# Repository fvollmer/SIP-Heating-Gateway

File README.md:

SIP Heating Gateway
====================

This device allows you to control the heating (or any other device) by calling in and using an interactive voice menu. In case of a power loss the last state will be restored as soon as the power is back. The software is build to survive unexpected power losses.

The heart of the system is a Raspberry pi with a custom hat to provide 12V to an external relay. On this Raspberry pi a custom embedded linux is used to to control the 12V via a small shell script. It connects via ethernet to the a SIP server (e.g. a fritzbox router or your isp). The heavy lifting for the SIP connection and the voice menu is done by asterisk, which uses the already mentioned shell script to switch a gpio pin. The linux system is build with buildroot and the hole image image is less than 200MB and boots in a few seconds.

The linux system on the raspberry pi is configured to use the micro sd card as read only storage. This should prevent damage on power failure. The only exception is a persitent partition, which is used to save the current state. This state will be restored in case of a power failure. The partition should also be safe from corruption due to the mount parameters and the infrequent writes.

## Usage

Connect Power (5V via micro-USB and 12V), ethernet and the output to the relay. After bootup the device accepts incoming calls.

Call the device,  wait until pickup and follow the voice instructions:
1. Enter the PIN and press `#`
2. Press `1` to turn the heating on, `2` to turn the heating off, `3` to get the status of the heating
3. Repeat step 2, or hang up

After a timeout the caller will be disconnected automatically.

```
                                               5V (micro USB)
                                                |
                                                v
+-----------------+                      +----------------+              +----------+
| router / switch | SIP (over ethernet)  | Raspberry Pi   | 12V Switched | Relay of |
| e.g. fritzbox   |<-------------------->| (with 12V hat) |------------->| heating  |
+-----------------+                      +----------------+              +----------+
                                                ^
                                                |
                                              12 V
```

## Configuration
The custom embedded system is based on buildroot. The behaviour at a call is controlled by [Asterisk](https://www.asterisk.org/). There are two main configuration files:
 * `/etc/asterisk/sip.conf`
   SIP server configuration
 * `/etc/asterisk/extensions.conf`
   Dialplan (phone menu, pin)

The configuration files can be adjusted by changing the files of the overlay (`br-external/board/raspberrypi-heating-control/rootfs-overlay`). Asterisk is configured to only use a minimal amount of modules. Modify `/etc/asterisk/modules.conf` if necessary.

There is a watchdog script (`/opt/heatingControl/asterisk_wdog`) that monitors the peers and registry and will restart asterisk in case of failures. It is automatically started at boot via `/etc/init.d/S55asterisk_wdog`. You probably want to stop it to configure asterisk and start it after the finished configuration.

For maintenace and debugging it is possible to connect to the device via a serial connection (115200 8N1) or HDMI. The system is by default read-only. To modify the file system it has to be remounted (`mount -o remount,rw /`). The login data is:

 * username: "root"
 * password: "" (There is no root password. This is no problem, because there is no way to login remotely)

## How to build the sd card image
You can build the sd card image yourself by cross compiling it on your pc. Depending on your hardware configuration this may take a while. Simply follow these steps:
1. Clone repository (use `--recursive` to get buildroot submodule)
2. Change into software folder (`cd software`)
3. `make BR2_EXTERNAL=$PWD/br-external -C buildroot raspberrypi23-heating-control_defconfig`
4. `make -C buildroot`
5. write `buildroot/output/images/sdcard.img` to sd card (e.g. `dd if=buildroot/output/images/sdcard.img of=/dev/mmcblk0 bs=1M && sync`)

## Hardware
You don't need any special hardware for this. The raspberry pi will just toggle one of the GPIO PINs (see `/opt/heatingControl/controlheating` for details).

The author of this project wants to switch a 12V relay and has designed a hat for this task. This hat is designed to take quite a bit of abuse like e.g. short circuit, reverse power, ESD etc. and can supply 5-24V with up to 1.5A from an external power supply. In practice it should also tolerate higher voltages and currents, but you probably want to check the schematic and datasheets to push the limits. Further it has a manual override switch in case of software issues or a failure of the raspberry pi. Simplified schematic:

Full schematic:

The hardware is designed to fit nicely into a HighPi Case, which has all necessary cutouts and can be mounted on a wall.

## Good to know
 * This system uses [Buildroot](https://buildroot.org/) to create a custom embedded system. This provides more flexibility and allows more customization than a stripped down raspbian. The complete image is just a little bigger than 100MB.
 * Connect via 3.3V serial (115200 8N1) or connect an external monitor via HDMI and use a usb keyboard
 * The heating control script is `/opt/heatingControl/controlheating`
 * The root system is read only. It can be mounted as rw (`mount / -o remount,rw`), but this is mainly recommanded for testing and maybe the initial configuration. Every change can be integrated into `br-external`. This way the image can be build in a repeatable way.
 * There is a small persistent storage partition at the sd card. It is mounted at boot via fstab at `/media/persistent/`. The mount options `rw,sync,data=journal,barrier=1,noatime,commit=1` were choosen to avoid data corruption and wear of the sd card. It is only used to store store the current state at `/media/persistent/last_state` and to restore it after a power loss. On every boot `/etc/init.d/S10restorestate` tries to restore the last state. 
 * To debug problems with asterisk it might be useful to connect to a running asterisk in verbose mode: `asterisk -rvvvv`. You can enable SIP debug mode with `sip set debug on`.
 * Any file can be added/overwritten by adding it ot the rootfs overlay at `br-external/board/raspberrypi2-heating-control/rootfs-overlay/`. 
 * The asterisk configuration files can be found at `/etc/asterisk`. The build process automatically deploys the default configuration files. The overlay is used to overwrite them.
    - SIP configuration file: `/etc/asterisk/sip.conf`
    - Dialplan (phone menu, pin): `/etc/asterisk/extensions.conf`
 * The buildroot configuration is based on the raspberry pi 2 configuration with additions to make it compatible with the raspberry pi 3. Other version can easily be added.
 * eth0 is managed by ifplugd (provided by busybox), which will automatically ifup/ifdown the interface if a network cable is connected/disconnected
 * The dhcp client was configured to run in the background. This is useful if the network link isn't ready when we try to get an ip address. This archived with a custom busybox configuration with the option `CONFIG_IFUPDOWN_UDHCPC_CMD_OPTIONS=-R -b -O search"`. The option `-b` sets udhcpc to run in the background. (`-R` is release on exit, `-O search` enables domain search option RFC 3397)
 * Busybox is configured to ship non default packages:
   - `rx` (in case we want to transfer a file via serial) 
   - `ifplugd` (see above)
 * Aterisk logs to syslog, this avoids filling up our tmpfs. Further cdr (call detail record) is disabled (`/etc/asterisk/cdr.conf`). Busybox rotates syslog for us (CONFIG_FEATURE_ROTATE_LOGFILE)
 * The hardware watchdog of the raspberry pi (bcm2835_wdt) is used to restart the system in case the system locks up. `/etc/init.d/S15watchdog` starts the watchdog at boot and periodically writes to `/dev/watchdog`.

## Overview of files
```
├──.github/workflows
├──audio-gen
├──hardware
└──software
   ├──buildroot
   └──br-external
      ├── board
      │   └── raspberrypi2-heating-control
      │       ├── genimage-raspberrypi2-heating-control.cfg
      │       ├── post-build.sh
      │       ├── post-image.sh
      │       └── rootfs-overlay
      │           └── <config files and scripts>
      ├── Config.in
      ├── configs
      │   └── raspberrypi2-heating-control_defconfig
      ├── external.desc
      └── external.mk
```

 * `.github/workflows` automatic build files
 * `audio-gen` infos about the audio file generation for the interactive voice menu
 * `hardware` pcb files for the 12V hat
 * `buildroot` git submodule of [buildroot](https://buildroot.org/)
 * `br-external` external overlay module for buildroot with all configuration and software files to build our custom linux

## Test cases

After making changes to the image, I like to test and verify that nothing broke by accident. The following test cases prooved to be useful. For now testing is done manually, but it would be an interesting idea to automate them.

 * Check basic functionality
   1. Start Rasbperry Pi with everything connected (including network)
   2. Call and interact with the voice menu
   3. Check authentication, automatic timeout, turn heating on/off, check status of heating
 * Check if state is restored on power loss
   1. Start Rasbperry Pi with everything connected (including network)
   2. Turn heating on
   3. Disconnect power, reconnect power
   4. Check if heating is automatically turned on while booting
   5. Repeat for heating off
 * Simulate power outage
   1. Disconnect Raspberry Pi AND the network infrastructure power
   2. Reconnect everything to power
   3. Check if Raspberry Pi can be called
 * Start Raspberry Pi without network and connect it later
   1. Start Raspberry Pi without network connection
   2. Wait 5 minutes
   3. Connect network connection
   4. Wait 5 minutes (asterisk watch dog will restart asterisk after like 4 minutes)
   5. Check if Raspberry Pi can be called

The previous checks are usually enough, but here are some more:

 * Check ifplugd
   1. Disconnect ethernet cable from running Pi
   2. Check if `ifconfig` if ip address is gone (takes a few seconds)
   3. Reconnect ethernet cable
   4. Check with `ifconfig` if we get a dhcp lease
 * Check asterisk watchdog
   1. Note current PID of asterisk: `pgrep -x asterisk`
   2. Disconnect ethernet cable from running Pi
   3. Check if watchdog complains at syslog (`/var/log/messages`), watchdog only checks asterisk once every 60 seconds
   4. Check if watchdog restarts asterisk after about 4 minutes by comparing the PID
 * Check if syslog is rotated
   1. run `while true; do logger hello; done` for some moments
   2. check if `/var/log/messages` is rotated to `/var/log/messages.0` and if file size is small (like 200kB)

## Enhancement Ideas
 * Add an ssh server to make maintenance easier (at the moment you have to connect via serial or connect your Keyboard and display directly). This ssh server could be enabled by a jumper to enable a maintenance mode.
 * Don't run asterisk as root. This sounds simple in theory, but the user needs permissions to write to /sys/class/gpio. The best way to archive this is probably to use `mdev` together with the `devtmpfs`. On the other hand it won't enhance the security a lot, since asterisk is the only service on this device.

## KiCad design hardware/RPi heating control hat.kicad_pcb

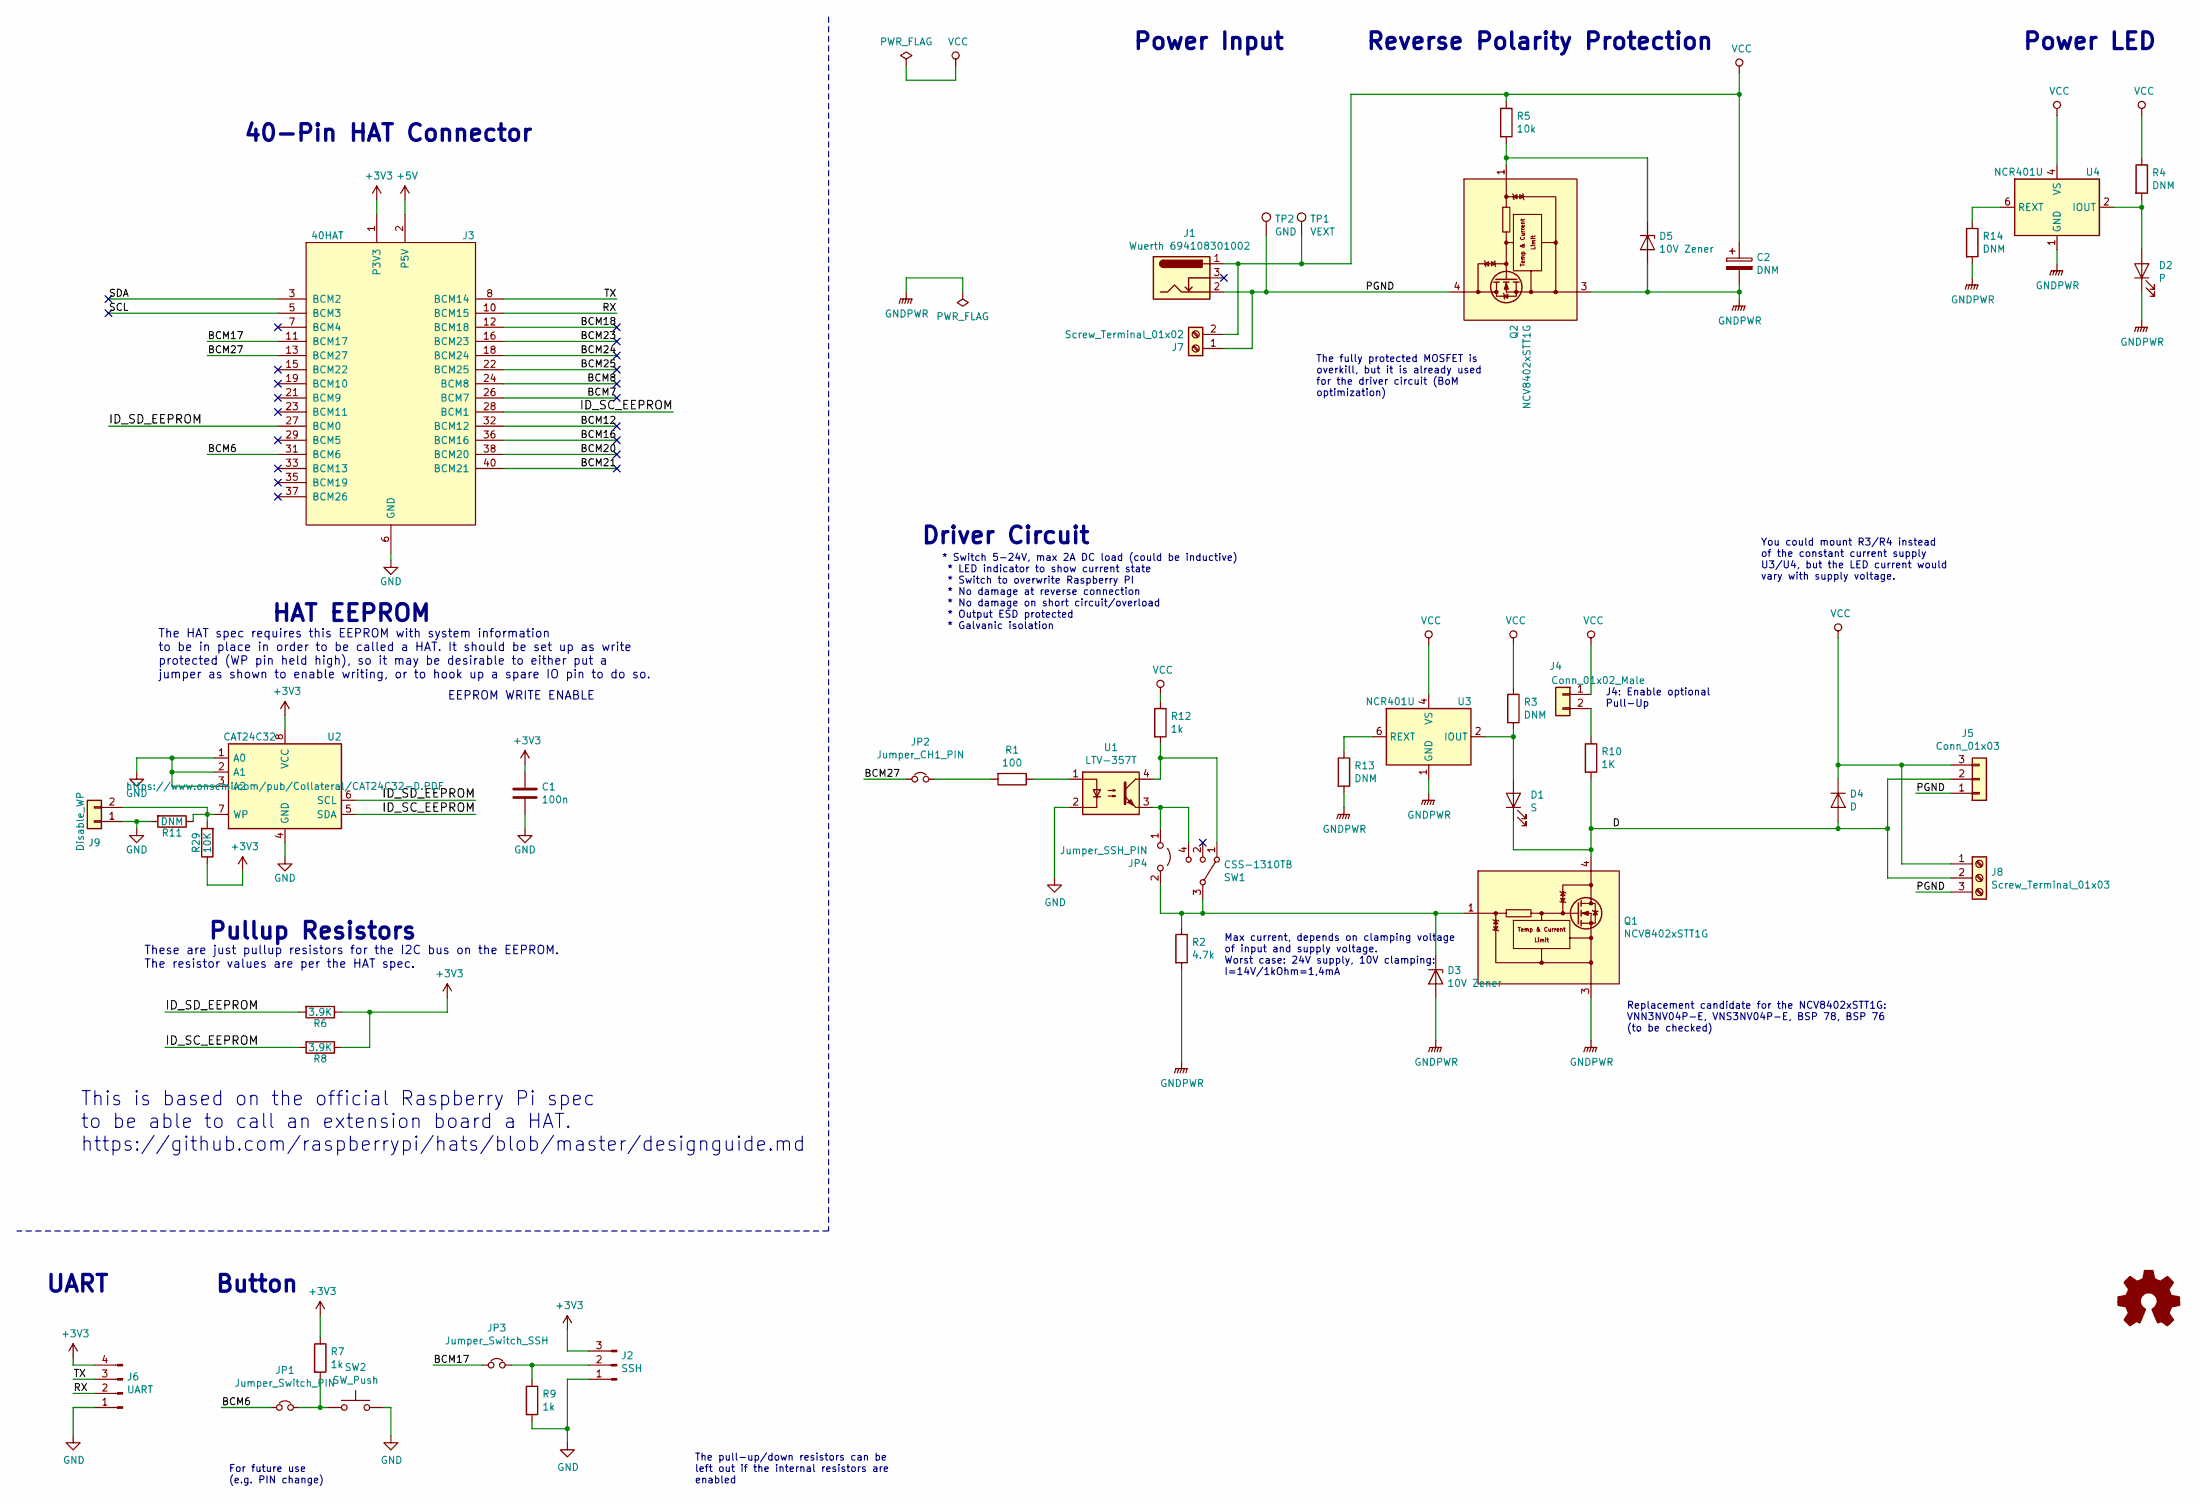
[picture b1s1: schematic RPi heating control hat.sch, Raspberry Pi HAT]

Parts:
C1: 100n; C_0603_1608Metric_Pad1.05x0.95mm_HandSolder
C2: DNM; CP_Elec_6.3x7.7
D1: S; LED_0603_1608Metric_Castellated; Digikey# 732-4971-1-ND
D2: P; LED_0603_1608Metric_Castellated; Digikey# 732-4978-1-ND
D3, D5: 10V Zener; D_SOD-123; Digikey# BZT52C10-TPMSCT-ND
D4: D; D_SMB-SMC_Universal_Handsoldering; Digikey# MBRS340T3GOSCT-ND
J1: Wuerth 694108301002; BarrelJack_Wuerth_6941xx301002; Digikey# 732-5934-ND
J2: SSH; PinHeader_1x03_P1.27mm_Vertical
J3: 40HAT; Raspberry_Pi_Addon_THT_With_Cutouts; Digikey# ?
J4: Conn_01x02_Male; PinHeader_1x02_P1.27mm_Vertical
J5: Conn_01x03; WAGO_250-403_1x03_P2.5
J6: UART; PinHeader_1x04_P1.27mm_Vertical
J7: Screw_Terminal_01x02; PhoenixContact_MSTBA_2,5_2-G_1x02_P5.00mm_Horizontal; Digikey# 277-1117-ND, 277-1000-ND
J8: Screw_Terminal_01x03; PhoenixContact_MSTBA_2,5_3-G_1x03_P5.00mm_Horizontal; Digikey# 277-1107-ND, 277-1012-ND
J9: Disable_WP; PinHeader_1x02_P2.54mm_Vertical
JP1: Jumper_Switch_PIN; SolderJumper-2_P1.3mm_Bridged_RoundedPad1.0x1.5mm
JP2: Jumper_CH1_PIN; SolderJumper-2_P1.3mm_Bridged_RoundedPad1.0x1.5mm
JP3: Jumper_Switch_SSH; SolderJumper-2_P1.3mm_Bridged_RoundedPad1.0x1.5mm
JP4: Jumper_SSH_PIN; SolderJumper-2_P1.3mm_Open_RoundedPad1.0x1.5mm
LOGO1: Logo_Open_Hardware_Small; OSHW-Symbol_6.7x6mm_Copper
Q1, Q2: NCV8402xSTT1G; SOT-223; Digikey# NCV8402ASTT1GOSCT-ND
R1: 100; R_0603_1608Metric_Pad1.05x0.95mm_HandSolder
R2: 4.7k; R_0603_1608Metric_Pad1.05x0.95mm_HandSolder
R3, R4, R11, R13, R14: DNM; R_0603_1608Metric_Pad1.05x0.95mm_HandSolder
R5: 10k; R_0603_1608Metric_Pad1.05x0.95mm_HandSolder
R6, R8: 3.9K; R_0603_1608Metric_Pad1.05x0.95mm_HandSolder
R7, R9, R12: 1k; R_0603_1608Metric_Pad1.05x0.95mm_HandSolder
R10: 1K; R_0603_1608Metric_Pad1.05x0.95mm_HandSolder
R29: 10K; R_0603_1608Metric_Pad1.05x0.95mm_HandSolder
SW1: CSS-1310TB; CSS-131XB; Digikey# 563-1095-1-ND
SW2: SW_Push; SW_Push_1P1T_NO_6x6mm_H9.5mm
TP1: VEXT; TestPoint_Pad_D1.0mm
TP2: GND; TestPoint_Pad_D1.0mm
U1: LTV-357T; SO-4_4.4x3.6mm_P2.54mm; Digikey# 160-1339-1-ND
U2: CAT24C32; SOIC-8_3.9x4.9mm_P1.27mm; Digikey# CAT24C32WI-GT3CT-ND
U3, U4: NCR401U; SC-74-6_1.5x2.9mm_P0.95mm; Digikey# 1727-2253-1-ND

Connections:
+3V3: C1.1, J2.3, J3.1 (P3V3), J3.17 (P3V3), J6.4, R6.1, R7.1, R8.1, R29.1, U2.8 (VCC)
+5V: J3.2 (P5V), J3.4 (P5V)
/BCM6: J3.31 (BCM6), JP1.1
/BCM7: J3.26 (BCM7)
/BCM8: J3.24 (BCM8)
/BCM12: J3.32 (BCM12)
/BCM16: J3.36 (BCM16)
/BCM17: J3.11 (BCM17), JP3.1
/BCM18: J3.12 (BCM18)
/BCM20: J3.38 (BCM20)
/BCM21: J3.40 (BCM21)
/BCM23: J3.16 (BCM23)
/BCM24: J3.18 (BCM24)
/BCM25: J3.22 (BCM25)
/BCM27: J3.13 (BCM27), JP2.1
/D: D1.1 (K), D4.2 (A), J5.2, J8.2, Q1.2 (D), Q1.4 (D), R10.2
/ID_SC_EEPROM: J3.28 (BCM1), R8.2, U2.5 (SDA)
/ID_SD_EEPROM: J3.27 (BCM0), R6.2, U2.6 (SCL)
/PGND: J1.2, J5.1, J7.1, J8.3, Q2.2 (D), Q2.4 (D), TP2.1
/RX: J3.10 (BCM15), J6.2
/SCL: J3.5 (BCM3)
/SDA: J3.3 (BCM2)
/TX: J3.8 (BCM14), J6.3
GND: C1.2, J2.1, J3.6 (GND), J3.9 (GND), J3.14 (GND), J3.20 (GND), J3.25 (GND), J3.30 (GND), J3.34 (GND), J3.39 (GND), J6.1, J9.1, R9.2, R11.2, SW2.2, U1.2, U2.1 (A0), U2.2 (A1), U2.3 (A2), U2.4 (GND)
GNDPWR: C2.2, D2.1 (K), D3.2 (A), D5.2 (A), Q1.3 (S), Q2.3 (S), R2.2, R13.2, R14.2, U3.1 (GND), U4.1 (GND)
unnamed: D1.2 (A), R3.2, U3.2 (IOUT), U3.3 (IOUT), U3.5 (IOUT)
unnamed: D2.2 (A), R4.2, U4.2 (IOUT), U4.3 (IOUT), U4.5 (IOUT)
unnamed: D3.1 (K), JP4.2 (B), Q1.1 (G), R2.1, SW1.3
unnamed: D5.1 (K), Q2.1 (G), R5.2
unnamed: J2.2, JP3.2, R9.1
unnamed: J4.2, R10.1
unnamed: J9.2, R11.1, R29.2, U2.7 (WP)
unnamed: JP1.2, R7.2, SW2.1
unnamed: JP2.2, R1.2
unnamed: JP4.1 (A), SW1.4, U1.3
unnamed: R1.1, U1.1
unnamed: R12.2, SW1.1, U1.4
unnamed: R13.1, U3.6 (REXT)
unnamed: R14.1, U4.6 (REXT)
VCC: C2.1, D4.1 (K), J1.1, J4.1, J5.3, J7.2, J8.1, R3.1, R4.1, R5.1, R12.1, TP1.1, U3.4 (VS), U4.4 (VS)

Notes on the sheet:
EEPROM WRITE ENABLE
Pullup Resistors
HAT EEPROM
40-Pin HAT Connector
The HAT spec requires this EEPROM with system information to be in place in order to be called a HAT. It should be set up as write protected (WP pin held high), so it may be desirable to either put a jumper as shown to enable writing, or to hook up a spare IO pin to do so.
These are just pullup resistors for the I2C bus on the EEPROM. The resistor values are per the HAT spec.
This is based on the official Raspberry Pi spec to be able to call an extension board a HAT. https://github.com/raspberrypi/hats/blob/master/designguide.md
UART
Power LED
Power Input
Driver Circuit
Replacement candidate for the NCV8402xSTT1G: VNN3NV04P-E, VNS3NV04P-E, BSP 78, BSP 76 (to be checked)
* Switch 5-24V, max 2A DC load (could be inductive) * LED indicator to show current state * Switch to overwrite Raspberry PI * No damage at reverse connection * No damage on short circuit/overload * Output ESD protected * Galvanic isolation
You could mount R3/R4 instead of the constant current supply U3/U4, but the LED current would vary with supply voltage.
Reverse Polarity Protection
Button
The fully protected MOSFET is overkill, but it is already used for the driver circuit (BoM optimization)
For future use (e.g. PIN change)
The pull-up/down resistors can be left out if the internal resistors are enabled
J4: Enable optional Pull-Up
Max current, depends on clamping voltage of input and supply voltage. Worst case: 24V supply, 10V clamping: I=14V/1kOhm=1,4mA

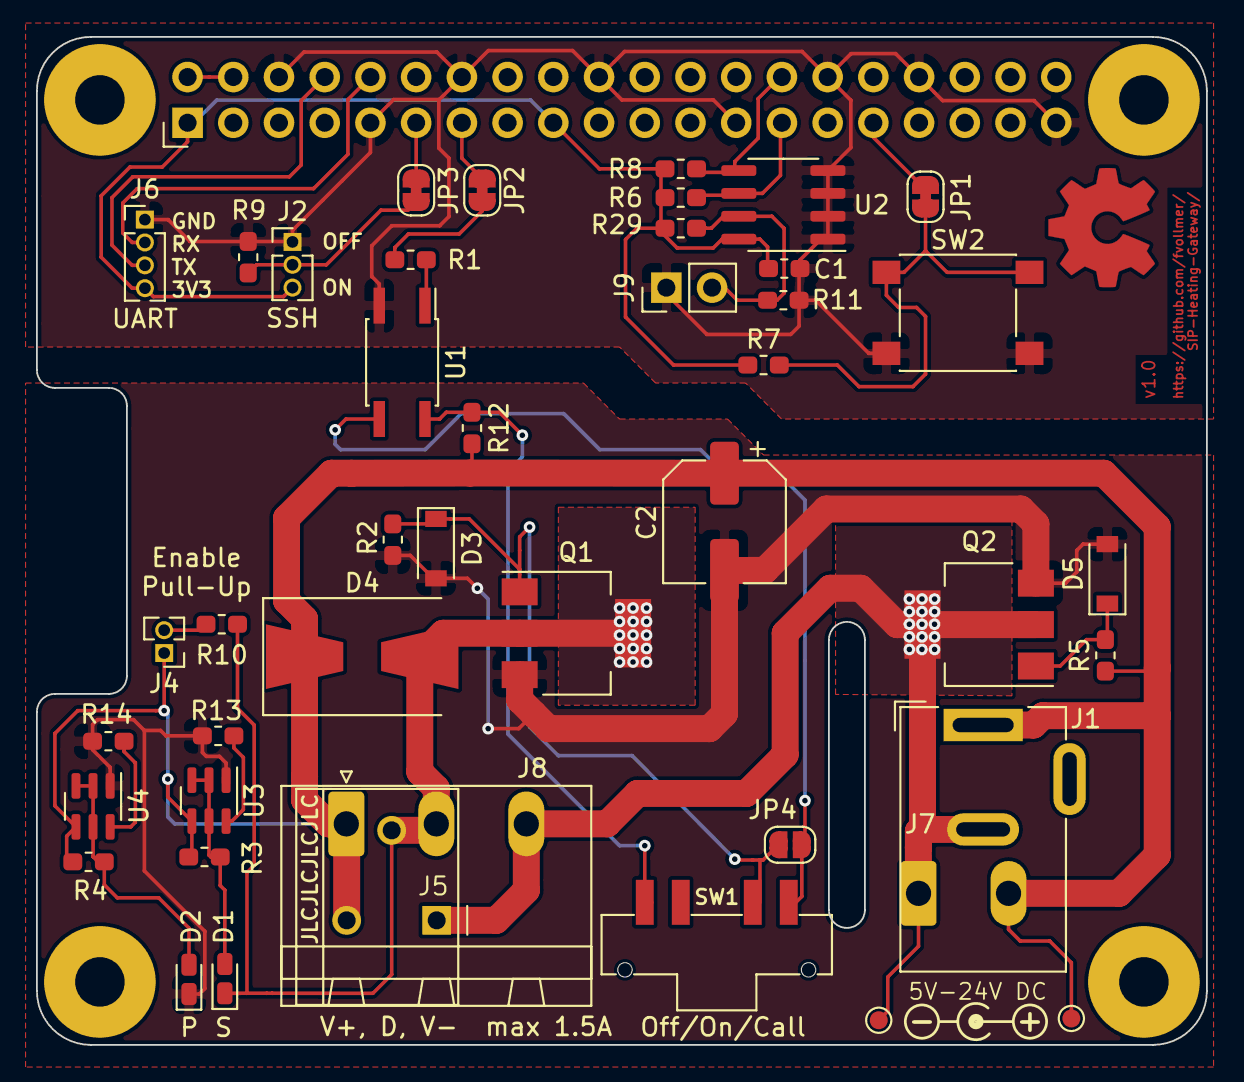
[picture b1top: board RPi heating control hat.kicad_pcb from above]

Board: 2 copper layers, 65.0 x 56.0 mm, 47 parts (0 on the bottom side), 28 nets.

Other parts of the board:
Polarity_Marker: Symbol_Barrel_Polarity

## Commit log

2019-11-27 add buildroot 2019.02.7 as submodule
2019-11-29 initial software
2019-11-29 Add licensing information and move files All files in br-external/board/raspberrypi2-heating-control/ were moved to br-external/board/raspberrypi-heating-control/ and a symlink was created to link fr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
2019-11-29 Turn heating on if last state can't be read (to be on the safe side)
2020-01-05 Add Hardware
2020-01-05 Minor change in simplified schematic (schematic -> circuit)
2020-01-17 Change control pin to 27 to match with pcb
2020-01-18 Run udhcpc in the background if link is not ready
2020-01-18 Adjust /etc/network/interfaces for new udhcpc configuration
2020-01-18 Add cd software to build instructions
2020-01-19 Enhance udhcpc options * remove "-n". I wasn't used since -b takes priority over -n (see busybox/networking/udhcp/dhcpc.c) * add "-O search" to enable domain search option (RFC 3397). This was the de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
2020-05-26 Fix path to S10restorestate in README
2020-05-26 fix documentation regarding flags of udhcpc
2020-05-26 Fix race condition with eth0 On the Raspberry Pi the ethernet may take a few seconds to show up (it is USB based) Our custom /etc/interfaces didn't include a "wait-delay" and therfor it could happen 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
2020-05-26 set ip of sip in /etc/hosts, attempt to register indefinitely, update README
2020-05-27 remove \n from issue
2020-05-28 add ifplugd and rx (via busybox) ifplugd is now handling eth0 to ifup/ifdown eth0 if the ethernet cable is plugged in or removed
2020-05-28 Add images
2020-05-28 add some more documentation to the README.md
2020-05-31 Add images to README.md
2020-06-04 add pgrep to image
2020-06-04 enhance asterisk startup script Try first to exit asterisk gracefully and then send the kill signal. Also wait a few seconds
2020-06-04 Let asterisk log to syslog, which is rotated by busybox
2020-06-04 Use hardware watchdog and remove logrotate (logrotate isn't needed since busybox can rotate the syslog by itself)
2020-06-04 fix comment in sip.conf comment start with a ; and not a #
2020-06-04 add asterisk watchdog, use default /etc/network/interfaces Now /etc/network/interfaces will initially try to up eth0 and then all plug events are handled by ifplugd
2020-06-04 Add tests to the README.md
2020-06-04 add schematic to README.md
2020-06-04 fix some formatting of README.md
2020-06-04 Use git describe to add version info to BR2_TARGET_GENERIC_ISSUE
2020-06-04 Add github action script for automatic builds and releases
2020-06-04 Integrate project name and version into asset names of releases
2020-06-04 Add build badge to README.md
2020-06-04 Fetch tags and old commits for automatic build git describe only works correctly if we fetch those
2020-06-05 Fix version string for assets of release, print version during build The version should only be e.g. v1.0 instead of refs.tag.v1.0
2020-06-05 Try to fetch tags manually in build script For some reason git describe wouldn't see the newest tag. Maybe this will fix the problem
2020-10-02 clean our defconfig, bump kernel version Our defconfig has now the same structure as raspberrypi2_defconfig. This should make future upgrades easier
2020-10-04 Add support for raspberry pi 3
2020-10-04 bump buildroot to 2020.02.6
